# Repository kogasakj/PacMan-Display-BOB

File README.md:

# PacMan-Display-BOB
Display interface board for AMS

Uses the 2.4" TFT LCD display and push buttons to provide a user interface for the battery packs.

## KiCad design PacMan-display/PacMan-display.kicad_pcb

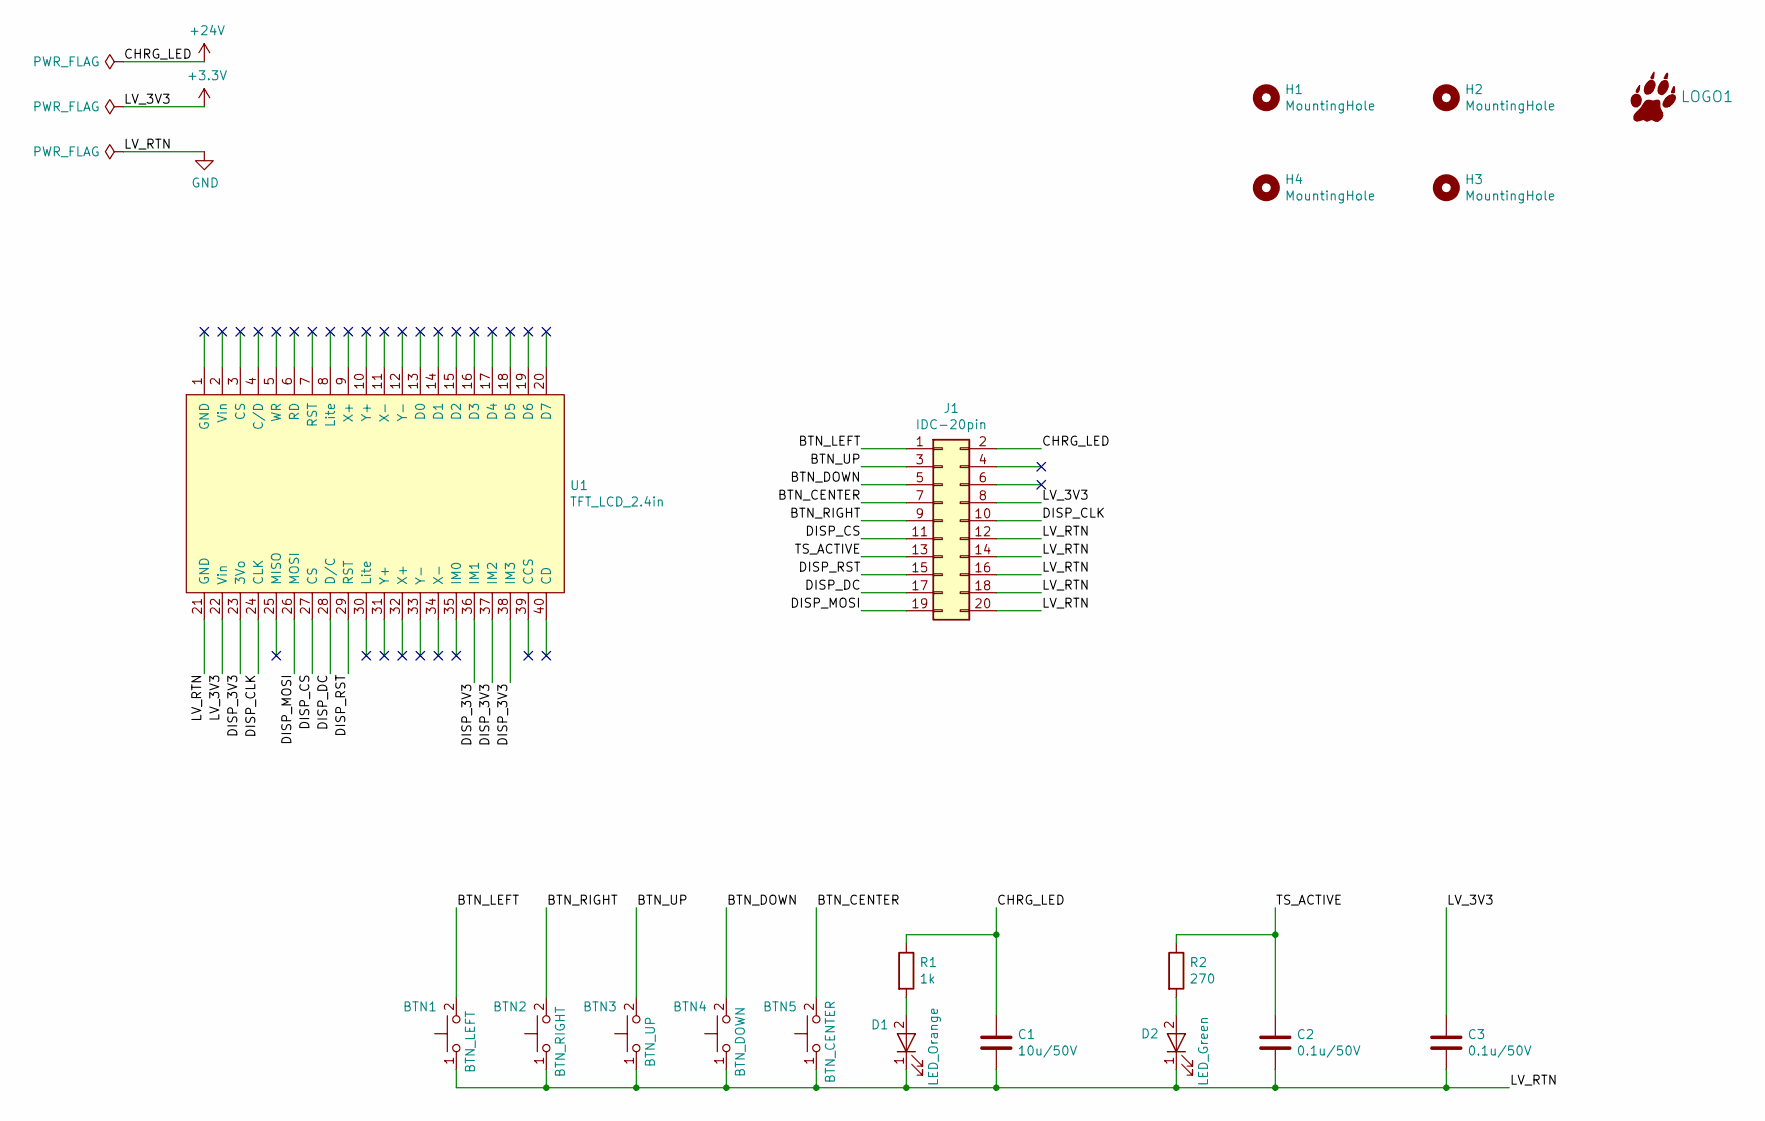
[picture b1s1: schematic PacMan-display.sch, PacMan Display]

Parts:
BTN1: BTN_LEFT; PushButton; Manufacturer Part 1.14100.5030000
BTN2: BTN_RIGHT; PushButton; Manufacturer Part 1.14100.5030000
BTN3: BTN_UP; PushButton; Manufacturer Part 1.14100.5030000
BTN4: BTN_DOWN; PushButton; Manufacturer Part 1.14100.5030000
BTN5: BTN_CENTER; PushButton; Manufacturer Part 1.14100.5030000
C1: 10u/50V; C_1210_3225Metric_Pad1.33x2.70mm_HandSolder
C2, C3: 0.1u/50V; C_0805_2012Metric_Pad1.18x1.45mm_HandSolder
D1: LED_Orange; LED_0805_2012Metric_Pad1.15x1.40mm_HandSolder
D2: LED_Green; LED_0805_2012Metric_Pad1.15x1.40mm_HandSolder; Manufacturer Part CMD17-21VGC/TR8
H1, H2, H3, H4: MountingHole; MountingHole_#4_NoPad
J1: IDC-20pin; IDC-Header_2x10_P2.54mm_Vertical
LOGO1: LeopardPawLogo; Paw
R1: 1k; R_0805_2012Metric_Pad1.20x1.40mm_HandSolder
R2: 270; R_0805_2012Metric_Pad1.20x1.40mm_HandSolder
U1: TFT_LCD_2.4in

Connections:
+3V3: C3.1, J1.8, U1.22 (Vin)
+24V: C1.1, J1.2, R1.1
/BTN_CENTER: BTN5.2, J1.7
/BTN_DOWN: BTN4.2, J1.5
/BTN_LEFT: BTN1.2, J1.1
/BTN_RIGHT: BTN2.2, J1.9
/BTN_UP: BTN3.2, J1.3
/DISP_3V3: U1.23 (3Vo), U1.36 (IM1), U1.37 (IM2), U1.38 (IM3)
/DISP_CLK: J1.10, U1.24 (CLK)
/DISP_CS: J1.11, U1.27 (CS)
/DISP_DC: J1.17, U1.28 (D/C)
/DISP_MOSI: J1.19, U1.26 (MOSI)
/DISP_RST: J1.15, U1.29 (RST)
/TS_ACTIVE: C2.1, J1.13, R2.1
GND: BTN1.1, BTN2.1, BTN3.1, BTN4.1, BTN5.1, C1.2, C2.2, C3.2, D1.1, D2.1, J1.12, J1.14, J1.16, J1.18, J1.20, U1.21 (GND)
unnamed: D1.2, R1.2
unnamed: D2.2, R2.2

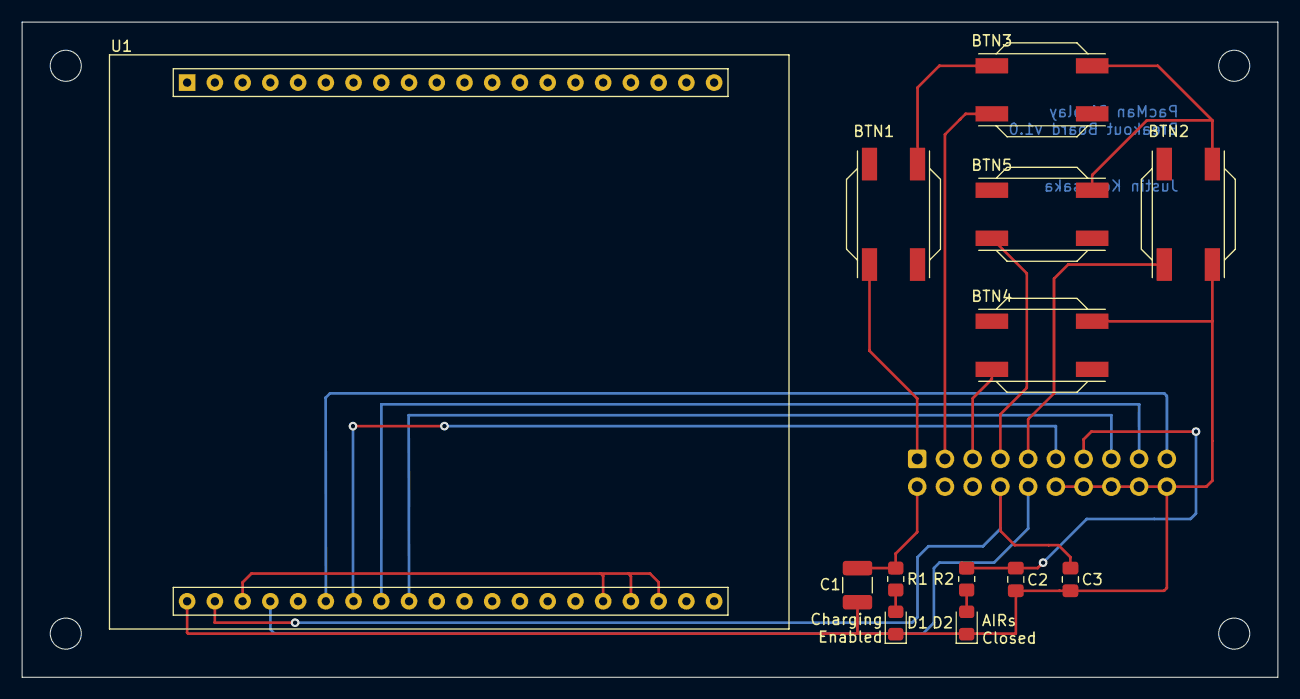
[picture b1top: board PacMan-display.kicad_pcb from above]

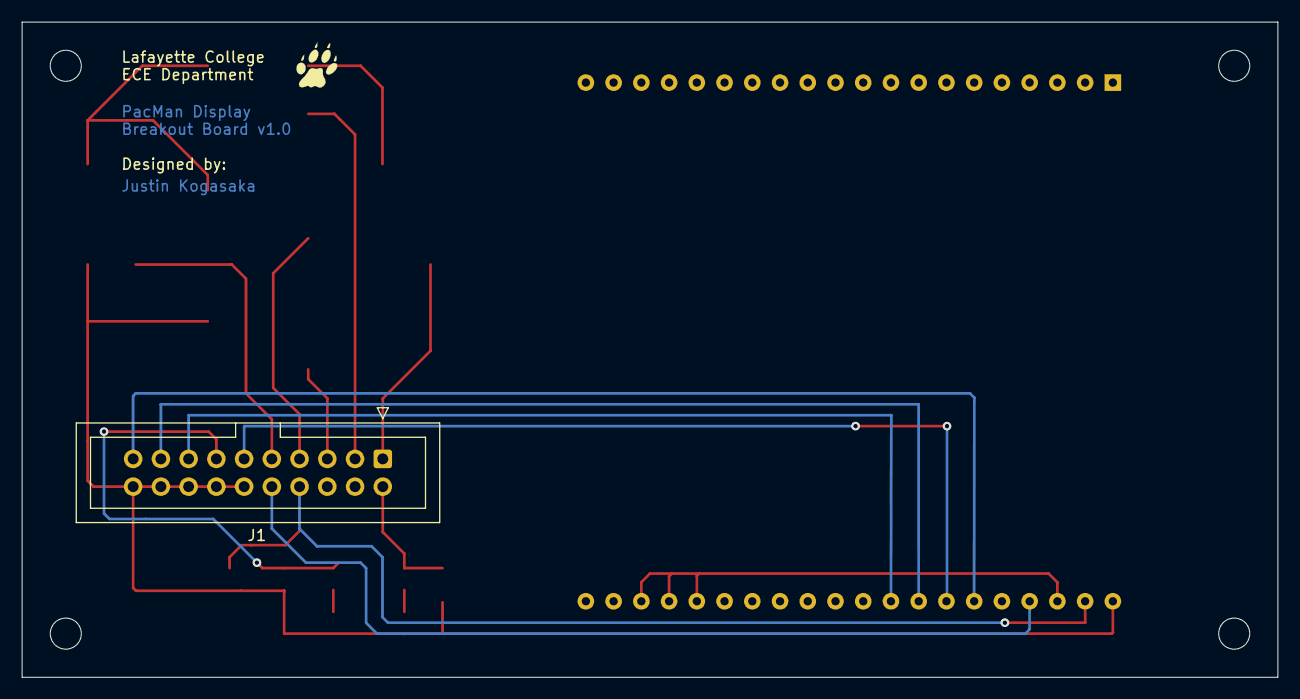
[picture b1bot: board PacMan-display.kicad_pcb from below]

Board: 2 copper layers, 115.0 x 60.0 mm, 19 parts (2 on the bottom side), 17 nets.
